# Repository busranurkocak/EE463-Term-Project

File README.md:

# EE463-Term-Project

Wind Turbine Controller (https://github.com/odtu/ee463/tree/master/Term%20Project)

Power Guide :Büşra Nur KOÇAK, Eren ÖZKARA, Yunus ÇAY

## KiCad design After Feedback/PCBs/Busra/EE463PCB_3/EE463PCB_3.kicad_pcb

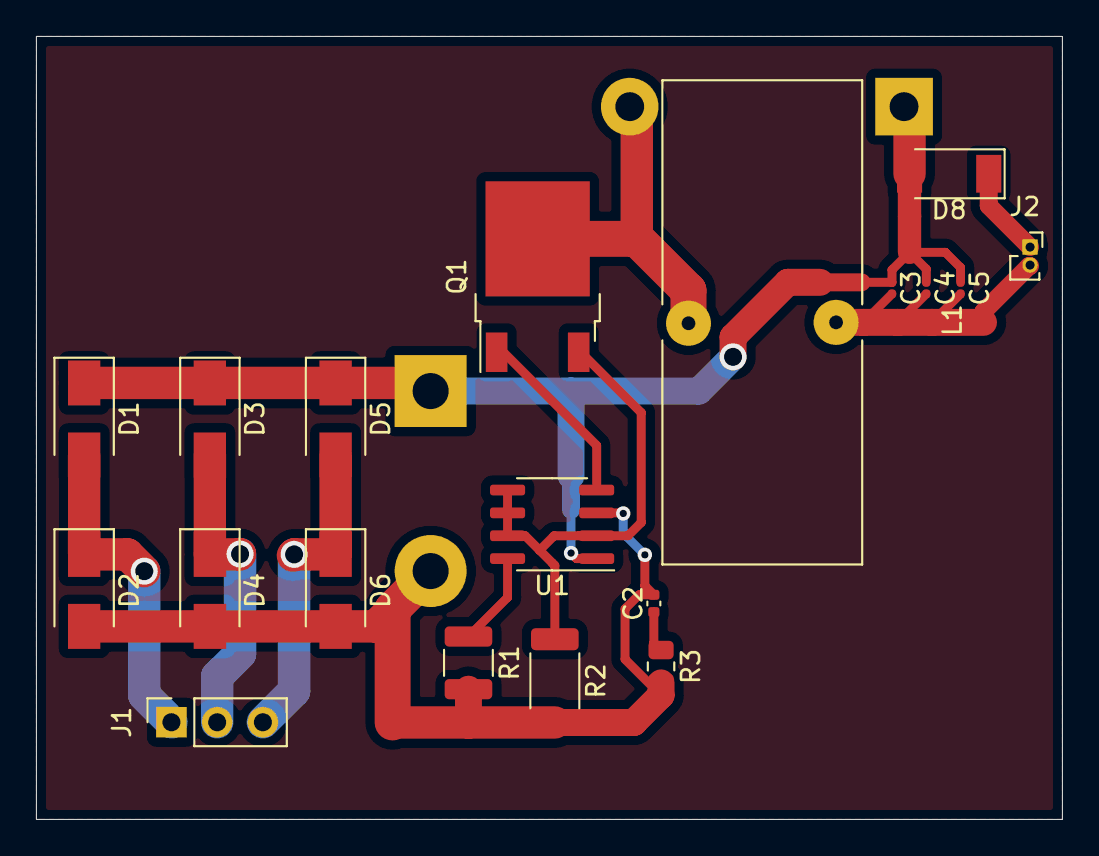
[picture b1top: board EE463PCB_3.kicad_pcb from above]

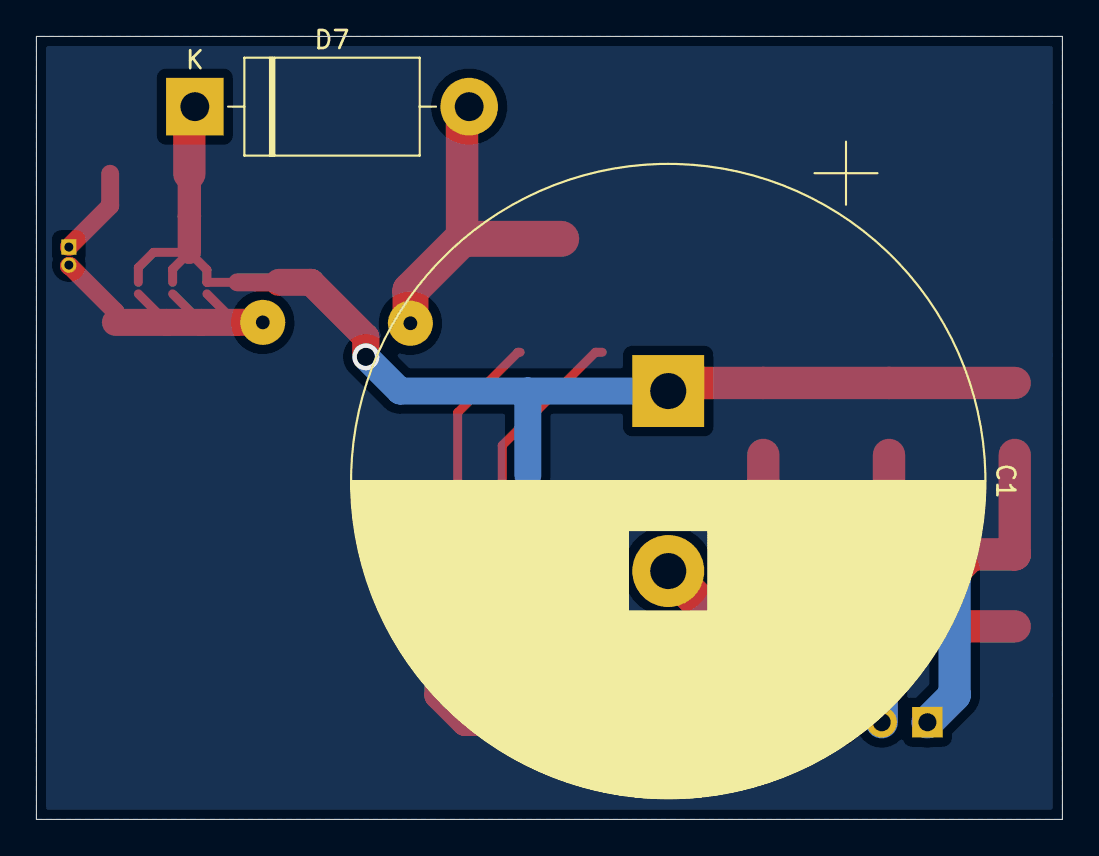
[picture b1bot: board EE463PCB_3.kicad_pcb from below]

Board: 2 copper layers, 57.0 x 43.5 mm, 21 parts (2 on the bottom side), 12 nets.

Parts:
C1: CP1; CP_Radial_D35.0mm_P10.00mm_SnapIn
C2: CP1; C_0402_1005Metric
C3, C4, C5: CP1; C_0201_0603Metric
D1, D2, D3, D4, D5, D6: US1G; D_SMA
D7: UF5404-E3/54; D_DO-201AD_P15.24mm_Horizontal
D8: PMEG6030EP,115; D_SOD-128
J1: Conn_01x03; PinSocket_1x03_P2.54mm_Vertical
J2: Conn_01x02; PinSocket_1x02_P1.00mm_Vertical
L1: L; T106-3_Inductor
Q1: IPD50R650CE; TO-252-2
R1: R; R_1210_3225Metric
R2: R; R_2010_5025Metric
R3: R; R_0805_2012Metric
U1: HV9961LG-G; SOIC-8_3.9x4.9mm_P1.27mm

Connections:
GND: C1.2, C2.2, D2.2, D4.2, D6.2, R1.2, R2.2, R3.2, U1.3
unnamed: C1.1, C3.1, C4.1, C5.1, D1.1, D3.1, D5.1, D7.1, D8.2, U1.1
unnamed: C2.1, R3.1
unnamed: C3.2, C4.2, C5.2, J2.2, L1.2
unnamed: D1.2, D2.1, J1.1
unnamed: D3.2, D4.1, J1.2
unnamed: D5.2, D6.1, J1.3
unnamed: D7.2, L1.1, Q1.2
unnamed: D8.1, J2.1
unnamed: Q1.1, U1.4
unnamed: Q1.3, R2.1, U1.2, U1.5, U1.6, U1.7
unnamed: R1.1, U1.8

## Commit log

2020-11-25 Hope to use Work Sheet
    work sheet file can be used to arrange whole important topics under a single roof.
2020-11-29 E-mail about Battery Charging
2020-12-05 The first draft of battery and PID test
2020-12-09 Generator model and Diode Rectifier Works
    The analytical calculations for diode rectifier and generator have been done.
2020-12-09 Inductor and Capacitor Calculations
2020-12-09 PCB Trials are added
2020-12-10 Example buck converter simulink file
2020-12-13 Diode Rectifier and PMSM Model
    The constructed circuit model for PMSM generator and diode rectifier can be found.
2020-12-13 A Buck converter capacitor and inductor calculator template have been added.
2020-12-13 Vin(max) modified as 250V.
2020-12-13 The First Trial of Battery+Buck Converter
    Values of capacitor and inductor should be adjusted
2020-12-13 Subblocks are combined
2020-12-14 Component Selection
    Google table for component selection has been constucted and link has been added
2020-12-19 Rectifier PCB is added
2020-12-24 Indcutor and Loss calculation code
    According to chosen componenets, the research for change in freq. have been started to decrease inductor in physical size.
2020-12-24 PI Controlled Buck Converter
2020-12-24 The First Version of the Report is uploaded
2020-12-24 PI Controlled Buck - 50Khz - Cap. Reselected
    Buck conv. with 50 khz have been controlled with PI controller. The Capactior value in LC filter have been reselected. The ESR value calculation has taken into consideration
2020-12-24 Reportv2 is uploaded and Final Simulationv2 is upgraded.
2020-12-25 Buck converter calculations and component selection have been added.
2020-12-25 Controller - Report written
    The part which is explanation of controller has been written.
2020-12-25 SLX file is redesigned.
    The messy componenets are combined in subblocks for complete circuit. Kp and Ki values are defined experimentally.
    Kp shouldn't exceed 6-7 and Ki can be defined according steady state error
2020-12-25 Add files via upload
    The first draft of the presentation is uploaded
2020-12-25 Rectifier part added to report
2020-12-25 Sw and Cond loss added to buck - Report
2020-12-25 Induction selection process have been added.
2020-12-25 Report is ready to check
2020-12-25 Formula values have been adjusted in table format.
2020-12-25 Simulation Report Completed!
2020-12-26 The Final Simulation Presentation is uploaded
2021-01-04 New rectifier components are added
2021-01-08 Components are updated
2021-01-08 Schematic of the PCB is uploaded
2021-01-09 New Components are added
2021-01-09 New components file is updated and PCB schematic is also updated
2021-01-11 Term Project PCB design version 1
2021-01-11 Updated PCB
2021-01-13 Copper Pour has been added on Routing Layers.
2021-01-14 PCB design updated.
2021-01-14 PCB updated
2021-01-15 Inductor Design information added.
2021-01-15 Explanation added for capacitor selectiıon process
2021-01-15 New component selection and BOM is added
2021-01-15 Extra information about topology is added
2021-01-15 no message
2021-01-15 PCB filed added.
2021-01-15 PCB Design explanation added.
2021-01-15 PCB report updated.
2021-01-15 Final Report _ Controller,Loss and Thermal
    The parts for controller, loss calcualation and thermal calculations are added
2021-01-15 Components graphs are added
2021-01-15 Final Report is uploaded
2021-01-15 Final Report is added
2021-01-21 Some files for presentation is uploaded
2021-01-23 Final Simulation model of hysteresis
2021-01-23 Final Presentation is uploaded
